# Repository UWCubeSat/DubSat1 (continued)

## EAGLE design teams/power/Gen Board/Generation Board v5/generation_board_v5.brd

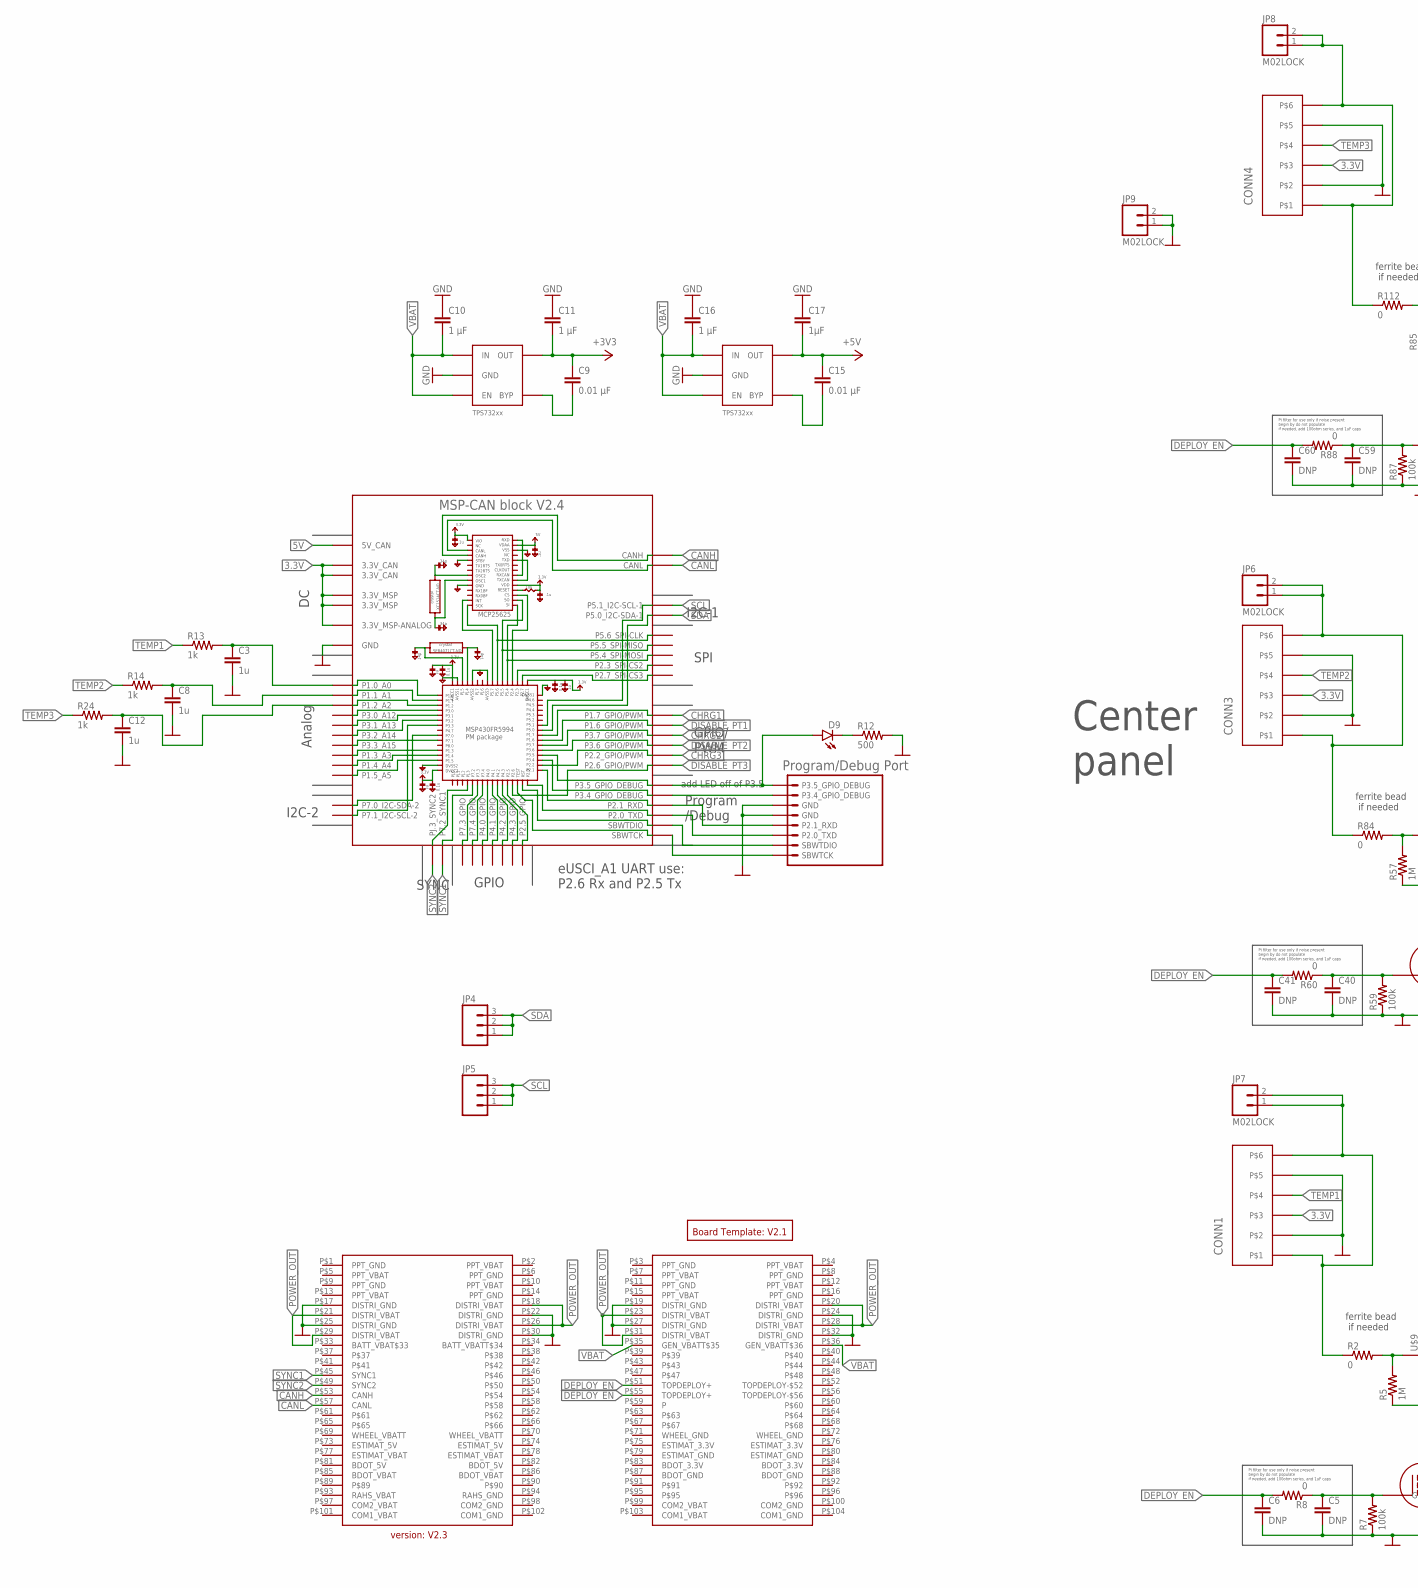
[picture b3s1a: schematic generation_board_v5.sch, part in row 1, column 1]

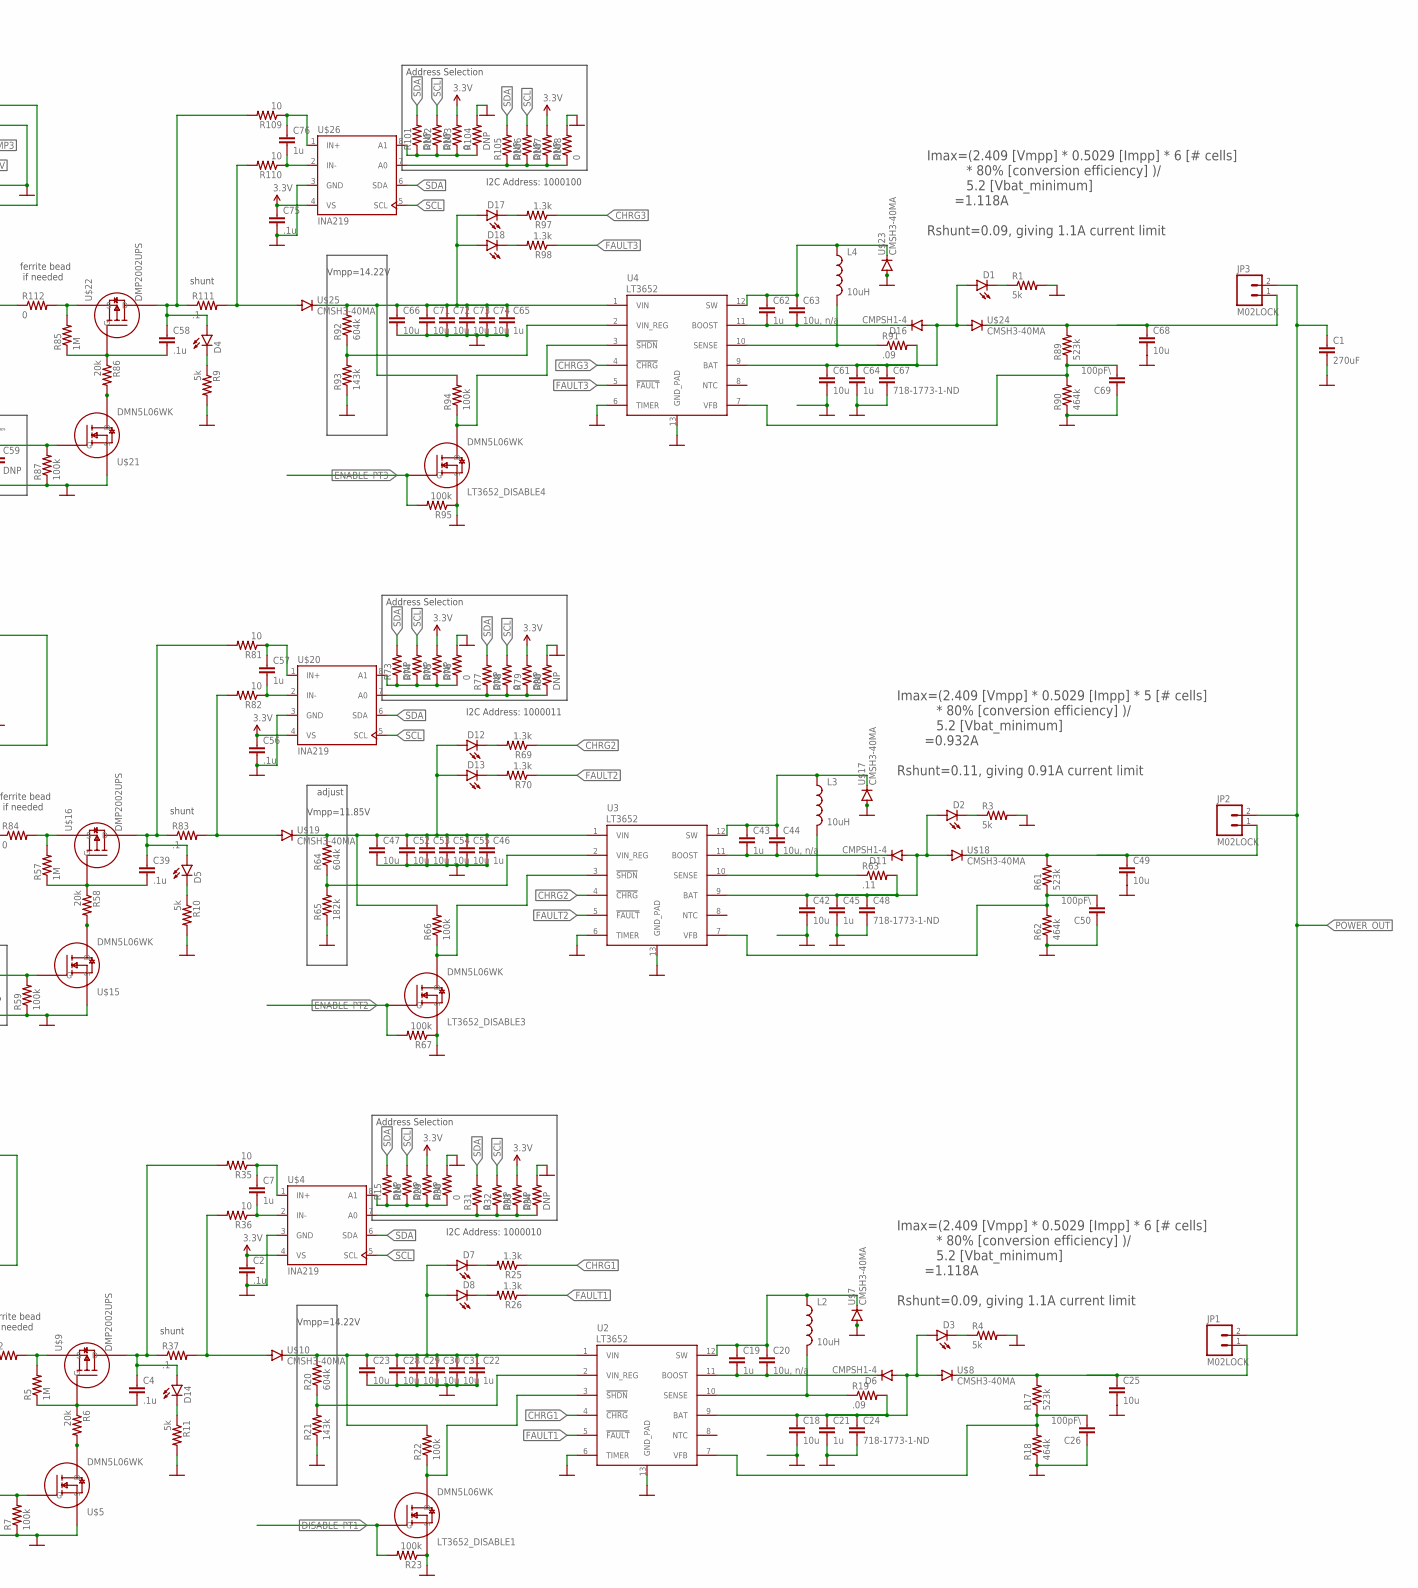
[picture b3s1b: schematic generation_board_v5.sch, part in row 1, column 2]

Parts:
BLK1: MSP-CAN_BLOCK
C1: 270uF; PANASONIC_SVPG
C2, C4, C39, C56, C58, C75: .1u; 0805
C3, C7, C8, C12, C19, C21, C22, C43, C45, C46, C57, C62, C64, C65, C76: 1u; 0805
C5, C6, C40, C41, C59, C60: DNP; 0805
C9, C15: 0.01 μF; 0805
C10, C11, C16: 1 μF; 0805
C17: 1μF; 0805
C18, C25, C42, C49, C61, C68: 10u; 0805
C20, C44, C63: 10u, n/a; 0805
C23, C28, C29, C30, C31, C47, C52, C53, C54, C55, C66, C71, C72, C73, C74: 10u; 1210
C24, C48, C67: 718-1773-1-ND; 2917
C26, C50, C69: 100pF\; 0805
CONN1, CONN3, CONN4: PICOLOCK_6
D1, D2, D3, D4, D5, D7, D8, D9, D12, D13, D14, D17, D18: LED; LED-1206
D6, D11, D16: CMPSH1-4; SOT23-3
JP1, JP2, JP3, JP6, JP7, JP8, JP9: M02LOCK; 1X02_LOCK
JP4, JP5: M03LOCK; 1X03_LOCK
L2, L3, L4: 10uH; VISHAY_SERIES_01
LT3652_DISABLE1, LT3652_DISABLE3, LT3652_DISABLE4: DMN5L06WK; SOT-323
R1, R3, R4, R9, R10, R11: 5k; 0805
R2, R8, R30, R31, R60, R76, R78, R84, R88, R103, R108, R112: 0; 0805
R5, R57, R85: 1M; 0805
R6, R58, R86: 20k; 0805
R7, R22, R23, R59, R66, R67, R87, R94, R95: 100k; 0805
R12: 500; 0805
R13, R14, R24: 1k; 0805
R15, R16, R29, R32, R33, R34, R73, R74, R75, R77, R79, R80, R101, R102, R104, R105, R106, R107: DNP; 0805
R17, R61, R89: 523k; 0805
R18, R62, R90: 464k; 0805
R19, R91: .09; R2010
R20, R64, R92: 604k; 0805
R21, R93: 143k; 0805
R25, R26, R69, R70, R97, R98: 1.3k; 0805
R35, R36, R81, R82, R109, R110: 10; 0805
R37, R83, R111: .1; R2010
R63: .11; R2010
R65: 182k; 0805
U2, U3, U4: LT3652; MSOP-12_GND
U5, U7: TPS732XX; SOT-23-5
U$1: PC104_CONNECTOR
U$2: BOARD_TEMPLATE1; BOARD_TEMPLATE
U$3: PROGRAM/DEBUG_PORT; 1X08_CONNECTOR
U$4, U$20, U$26: INA219; SOT-23-8
U$5, U$15, U$21: DMN5L06WK; SOT-323
U$7, U$8, U$10, U$17, U$18, U$19, U$23, U$24, U$25: CMSH3-40MA; SMA-DIODE
U$9, U$16, U$22: DMP2002UPS; POWERDI5060-8

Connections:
3.3V: BLK1.3.3V@CAN1 (3.3V_CAN), BLK1.3.3V@CAN2 (3.3V_CAN), BLK1.3.3V@MSP1 (3.3V_MSP), BLK1.3.3V@MSP2 (3.3V_MSP), BLK1.3.3V_ANALOG@MSP2 (3.3V_MSP-ANALOG), C2.1, C9.1, C11.2, C56.1, C75.1, CONN1.P$3, CONN3.P$3, CONN4.P$3, R29.2, R33.2, R75.2, R79.2, R103.2, R107.2, U5.P$5 (OUT), U$4.4 (VS), U$20.4 (VS), U$26.4 (VS)
5V: BLK1.5V (5V_CAN), C15.1, C17.2, U7.P$5 (OUT)
BAT1: C18.1, C21.1, C24.1, D3.A, D6.1 (A), R19.2, U2.9 (BAT), U$8.A
BAT2: C42.1, C45.1, C48.1, D2.A, D11.1 (A), R63.2, U3.9 (BAT), U$18.A
BAT3: C61.1, C64.1, C67.1, D1.A, D16.1 (A), R91.2, U4.9 (BAT), U$24.A
BOOST1: C19.2, C20.2, D6.3 (C), U2.11 (BOOST)
BOOST2: C43.2, C44.2, D11.3 (C), U3.11 (BOOST)
BOOST3: C62.2, C63.2, D16.3 (C), U4.11 (BOOST)
CANH: BLK1.CANH, U$1.P$53 (CANH)
CANL: BLK1.CANL, U$1.P$57 (CANL)
CHRG1: BLK1.P1.7_GPIO/PWM, R25.1, U2.4 (!CHRG)
CHRG2: BLK1.P3.7_GPIO/PWM, R69.1, U3.4 (!CHRG)
CHRG3: BLK1.P2.2_GPIO/PWM, R97.1, U4.4 (!CHRG)
DEPLOY_EN: C6.1, C41.1, C60.1, R8.2, R60.2, R88.2, U$1.P$51 (TOPDEPLOY+), U$1.P$55 (TOPDEPLOY+)
DISABLE_PT1: BLK1.P1.6_GPIO/PWM, LT3652_DISABLE1.1 (G), R23.2
DISABLE_PT2: BLK1.P3.6_GPIO/PWM
DISABLE_PT3: BLK1.P2.6_GPIO/PWM
ENABLE_PT2: LT3652_DISABLE3.1 (G), R67.2
ENABLE_PT3: LT3652_DISABLE4.1 (G), R95.2
FAULT1: R26.1, U2.5 (!FAULT)
FAULT2: R70.1, U3.5 (!FAULT)
FAULT3: R98.1, U4.5 (!FAULT)
GND: BLK1.GND@1 (GND), BLK1.GND@2 (GND), BLK1.GND@3 (GND), BLK1.GND@4 (GND), BLK1.GND@5 (GND), BLK1.GND@7 (GND), BLK1.GND@8 (GND), BLK1.GND@9 (GND), BLK1.GND@10 (GND), BLK1.GND@11 (GND), BLK1.GND@12 (GND), BLK1.GND@13 (GND), BLK1.GND@14 (GND), BLK1.GND@15 (GND), BLK1.GND@16 (GND), BLK1.GND@17 (GND), BLK1.GND@26 (GND), C1.NEG (2), C2.2, C3.2, C5.2, C6.2, C8.2, C10.1, C11.1, C12.2, C16.1, C17.1, C18.2, C21.2, C22.2, C23.2, C24.2, C25.2, C26.1, C28.2, C29.2, C30.2, C31.2, C40.2, C41.2, C42.2, C45.2, C46.2, C47.2, C48.2, C49.2, C50.1, C52.2, C53.2, C54.2, C55.2, C56.2, C59.2, C60.2, C61.2, C64.2, C65.2, C66.2, C67.2, C68.2, C69.1, C71.2, C72.2, C73.2, C74.2, C75.2, CONN1.P$2, CONN1.P$5, CONN3.P$2, CONN3.P$5, CONN4.P$2, CONN4.P$5, JP9.1, JP9.2, LT3652_DISABLE1.2 (S), LT3652_DISABLE3.2 (S), LT3652_DISABLE4.2 (S), R1.2, R3.2, R4.2, R7.1, R9.2, R10.2, R11.2, R12.2, R18.1, R21.1, R23.1, R30.2, R34.2, R59.1, R62.1, R65.1, R67.1, R76.2, R80.2, R87.1, R90.1, R93.1, R95.1, R104.2, R108.2, U2.6 (TIMER), U2.13 (GND_PAD), U3.6 (TIMER), U3.13 (GND_PAD), U4.6 (TIMER), U4.13 (GND_PAD), U5.P$2 (GND), U7.P$2 (GND), U$1.P$17 (DISTRI_GND), U$1.P$19 (DISTRI_GND), U$1.P$22 (DISTRI_GND), U$1.P$24 (DISTRI_GND), U$1.P$25 (DISTRI_GND), U$1.P$27 (DISTRI_GND), U$1.P$30 (DISTRI_GND), U$1.P$32 (DISTRI_GND), U$3.5 (GND), U$3.6 (GND), U$4.3 (GND), U$5.2 (S), U$7.A, U$15.2 (S), U$17.A, U$20.3 (GND), U$21.2 (S), U$23.A, U$26.3 (GND)
IN1: R2.2, R5.2, U$9.S1 (S), U$9.S2 (S), U$9.S3 (S)
IN2: R57.2, R84.2, U$16.S1 (S), U$16.S2 (S), U$16.S3 (S)
IN3: R85.2, R112.2, U$22.S1 (S), U$22.S2 (S), U$22.S3 (S)
INA219_A0_1: R31.1, R32.1, R33.1, R34.1, U$4.7 (A0)
INA219_A0_2: R77.1, R78.1, R79.1, R80.1, U$20.7 (A0)
INA219_A0_3: R105.1, R106.1, R107.1, R108.1, U$26.7 (A0)
INA219_A1_1: R15.1, R16.1, R29.1, R30.1, U$4.8 (A1)
INA219_A1_2: R73.1, R74.1, R75.1, R76.1, U$20.8 (A1)
INA219_A1_3: R101.1, R102.1, R103.1, R104.1, U$26.8 (A1)
INA219_IN+_1: C7.1, R35.1, U$4.1 (IN+)
INA219_IN+_2: C57.1, R81.1, U$20.1 (IN+)
INA219_IN+_3: C76.1, R109.1, U$26.1 (IN+)
INA219_IN-_1: C7.2, R36.1, U$4.2 (IN-)
INA219_IN-_2: C57.2, R82.1, U$20.2 (IN-)
INA219_IN-_3: C76.2, R110.1, U$26.2 (IN-)
INPUT_PANEL1: CONN1.P$1, CONN1.P$6, JP7.1, JP7.2, R2.1
INPUT_PANEL2: CONN3.P$1, CONN3.P$6, JP6.1, JP6.2, R84.1
INPUT_PANEL3: CONN4.P$1, CONN4.P$6, JP8.1, JP8.2, R112.1
LDO_3V3_BYP2: C9.2, U5.P$4 (BYP)
LDO_5V_BYP2: C15.2, U7.P$4 (BYP)
LOAD1: R36.2, R37.2, U$10.A
LOAD2: R82.2, R83.2, U$19.A
LOAD3: R110.2, R111.2, U$25.A
unnamed: C4.2, R5.1, R6.1, U$9.G
unnamed: C5.1, R7.2, R8.1, U$5.1 (G)
unnamed: BLK1.P3.5_GPIO_DEBUG, D9.A, U$3.8 (P3.5_GPIO_DEBUG)
unnamed: BLK1.P3.4_GPIO_DEBUG, U$3.7 (P3.4_GPIO_DEBUG)
unnamed: BLK1.P2.1_RXD, U$3.4 (P2.1_RXD)
unnamed: R6.2, U$5.3 (D)
unnamed: BLK1.P2.0_TXD, U$3.3 (P2.0_TXD)
unnamed: BLK1.SBWTDIO, U$3.2 (SBWTDIO)
unnamed: BLK1.SBWTCK, U$3.SBWTCK
unnamed: D1.C, R1.1
unnamed: D2.C, R3.1
unnamed: D3.C, R4.1
unnamed: D4.C, R9.1
unnamed: C39.2, R57.1, R58.1, U$16.G
unnamed: C40.1, R59.2, R60.1, U$15.1 (G)
unnamed: LT3652_DISABLE1.3 (D), R22.1, U2.3 (!SHDN)
unnamed: D8.C, R26.2
unnamed: D7.C, R25.2
unnamed: R58.2, U$15.3 (D)
unnamed: BLK1.P1.1_A1, C8.1, R14.2
unnamed: D9.C, R12.1
unnamed: LT3652_DISABLE3.3 (D), R66.1, U3.3 (!SHDN)
unnamed: D13.C, R70.2
unnamed: D12.C, R69.2
unnamed: D14.C, R11.1
unnamed: D5.C, R10.1
unnamed: C58.2, R85.1, R86.1, U$22.G
unnamed: C59.1, R87.2, R88.1, U$21.1 (G)
unnamed: R86.2, U$21.3 (D)
unnamed: LT3652_DISABLE4.3 (D), R94.1, U4.3 (!SHDN)
unnamed: D18.C, R98.2
unnamed: D17.C, R97.2
unnamed: BLK1.P1.2_A2, C12.1, R24.2
unnamed: BLK1.P1.0_A0, C3.1, R13.2
OUT1: C4.1, D14.A, R35.2, R37.1, U$9.D1 (D), U$9.D2 (D), U$9.D3 (D), U$9.D4 (D), U$9.D5 (D)
OUT2: C39.1, D5.A, R81.2, R83.1, U$16.D1 (D), U$16.D2 (D), U$16.D3 (D), U$16.D4 (D), U$16.D5 (D)
OUT3: C58.1, D4.A, R109.2, R111.1, U$22.D1 (D), U$22.D2 (D), U$22.D3 (D), U$22.D4 (D), U$22.D5 (D)
OUTPUT1: C25.1, JP1.1, R17.2, U$8.C
OUTPUT2: C49.1, JP2.1, R61.2, U$18.C
OUTPUT3: C68.1, JP3.1, R89.2, U$24.C
POWER_OUT: C1.POS (1), JP1.2, JP2.2, JP3.2, U$1.P$18 (DISTRI_VBAT), U$1.P$20 (DISTRI_VBAT), U$1.P$21 (DISTRI_VBAT), U$1.P$23 (DISTRI_VBAT), U$1.P$26 (DISTRI_VBAT), U$1.P$28 (DISTRI_VBAT), U$1.P$29 (DISTRI_VBAT), U$1.P$31 (DISTRI_VBAT)
SCL: BLK1.P5.1_I2C-SCL-1, JP5.1, JP5.2, JP5.3, R16.2, R32.2, R74.2, R78.2, R102.2, R106.2, U$4.5 (SCL), U$20.5 (SCL), U$26.5 (SCL)
SDA: BLK1.P5.0_I2C-SDA-1, JP4.1, JP4.2, JP4.3, R15.2, R31.2, R73.2, R77.2, R101.2, R105.2, U$4.6 (SDA), U$20.6 (SDA), U$26.6 (SDA)
SENSE1: L2.P$2 (2), R19.1, U2.10 (SENSE)
SENSE2: L3.P$2 (2), R63.1, U3.10 (SENSE)
SENSE3: L4.P$2 (2), R91.1, U4.10 (SENSE)
SW1: C19.1, C20.1, L2.P$1 (1), U2.12 (SW), U$7.C
SW2: C43.1, C44.1, L3.P$1 (1), U3.12 (SW), U$17.C
SW3: C62.1, C63.1, L4.P$1 (1), U4.12 (SW), U$23.C
SYNC1: BLK1.P7.2_SYNC1, U$1.P$45 (SYNC1)
SYNC2: BLK1.PJ.3_SYNC2, U$1.P$49 (SYNC2)
TEMP1: CONN1.P$4, R13.1
TEMP2: CONN3.P$4, R14.1
TEMP3: CONN4.P$4, R24.1
VBAT: C10.2, C16.2, U5.P$1 (IN), U5.P$3 (EN), U7.P$1 (IN), U7.P$3 (EN), U$1.P$35 (GEN_VBATT$35), U$1.P$36 (GEN_VBATT$36)
VFB1: C26.2, R17.1, R18.2, U2.7 (VFB)
VFB2: C50.2, R61.1, R62.2, U3.7 (VFB)
VFB3: C69.2, R89.1, R90.2, U4.7 (VFB)
VIN1: C22.1, C23.1, C28.1, C29.1, C30.1, C31.1, D7.A, D8.A, R20.2, R22.2, U2.1 (VIN), U$10.C
VIN2: C46.1, C47.1, C52.1, C53.1, C54.1, C55.1, D12.A, D13.A, R64.2, R66.2, U3.1 (VIN), U$19.C
VIN3: C65.1, C66.1, C71.1, C72.1, C73.1, C74.1, D17.A, D18.A, R92.2, R94.2, U4.1 (VIN), U$25.C
VIN_REG1: R20.1, R21.2, U2.2 (VIN_REG)
VIN_REG2: R64.1, R65.2, U3.2 (VIN_REG)
VIN_REG3: R92.1, R93.2, U4.2 (VIN_REG)

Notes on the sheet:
Pi filter for use only if noise present begin by do not populate if needed, add 100ohm series, and 1uF caps
Address Selection
ferrite bead if needed
shunt
adjust
Vmpp=14.22V
Center panel
Imax=(2.409 [Vmpp] * 0.5029 [Impp] * 6 [# cells] * 80% [conversion efficiency] )/ 5.2 [Vbat_minimum] =1.118A Rshunt=0.09, giving 1.1A current limit
Imax=(2.409 [Vmpp] * 0.5029 [Impp] * 5 [# cells] * 80% [conversion efficiency] )/ 5.2 [Vbat_minimum] =0.932A Rshunt=0.11, giving 0.91A current limit
Vmpp=11.85V
I2C Address: 1000010
I2C Address: 1000011
I2C Address: 1000100

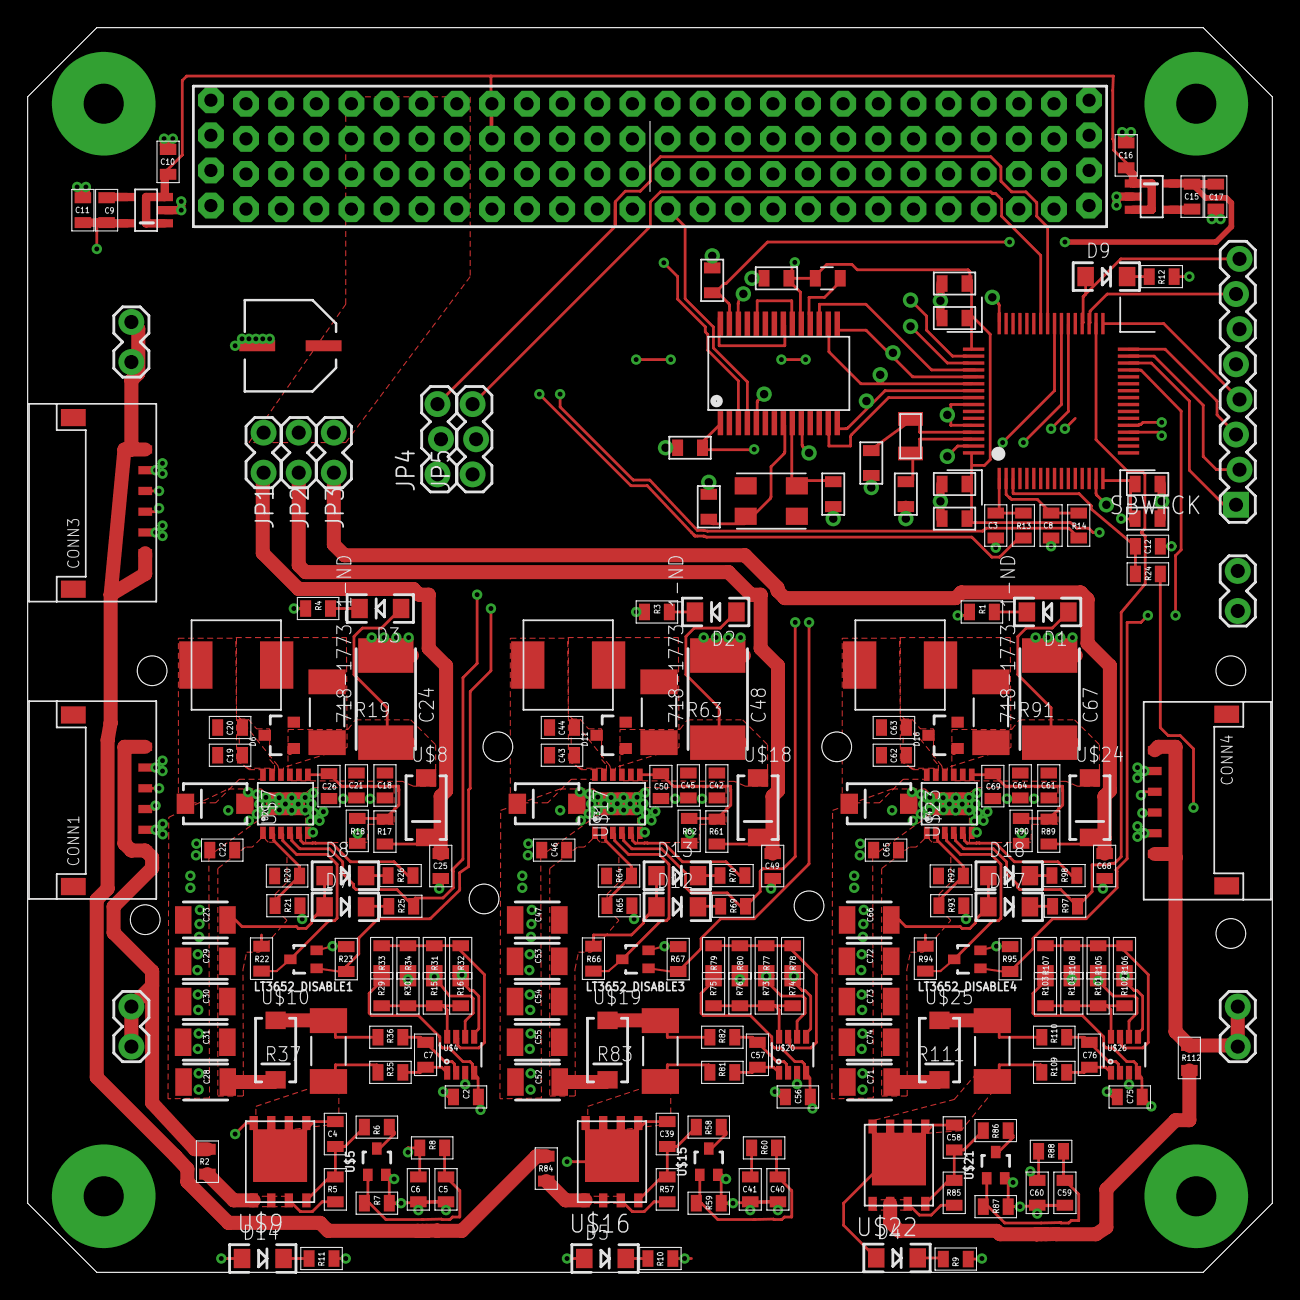
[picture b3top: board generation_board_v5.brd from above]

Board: 4 copper layers, 90.0 x 90.0 mm, 218 parts (0 on the bottom side), 108 nets.

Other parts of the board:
U$6, U$11, U$12, U$13, U$14, U$27, U$28, U$29: #2-56_BOLT_HOLE

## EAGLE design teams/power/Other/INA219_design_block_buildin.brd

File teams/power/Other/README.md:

This folder is for usefull resources such as eagle libraries, cam processors and such. Not for documentation

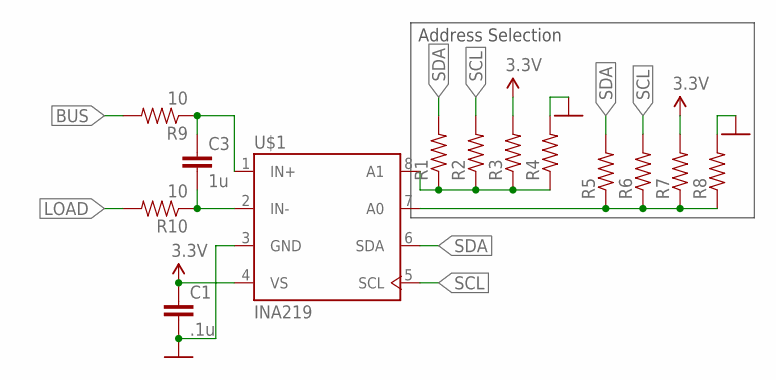
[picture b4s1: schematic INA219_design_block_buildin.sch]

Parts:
C1: .1u; 0805
C3: 1u; 0805
R1, R2, R3, R4, R5, R6, R7, R8: RESISTOR0805; 0805
R9, R10: 10; 0805
U$1: INA219; SOT-23-8

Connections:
3.3V: C1.1, R3.2, R7.2, U$1.4 (VS)
BUS: R9.2
GND: C1.2, R4.2, R8.2, U$1.3 (GND)
INA219_A0: R5.1, R6.1, R7.1, R8.1, U$1.7 (A0)
INA219_A1: R1.1, R2.1, R3.1, R4.1, U$1.8 (A1)
INA219_IN+: C3.1, R9.1, U$1.1 (IN+)
INA219_IN-: C3.2, R10.1, U$1.2 (IN-)
LOAD: R10.2
SCL: R2.2, R6.2, U$1.5 (SCL)
SDA: R1.2, R5.2, U$1.6 (SDA)

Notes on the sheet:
Address Selection

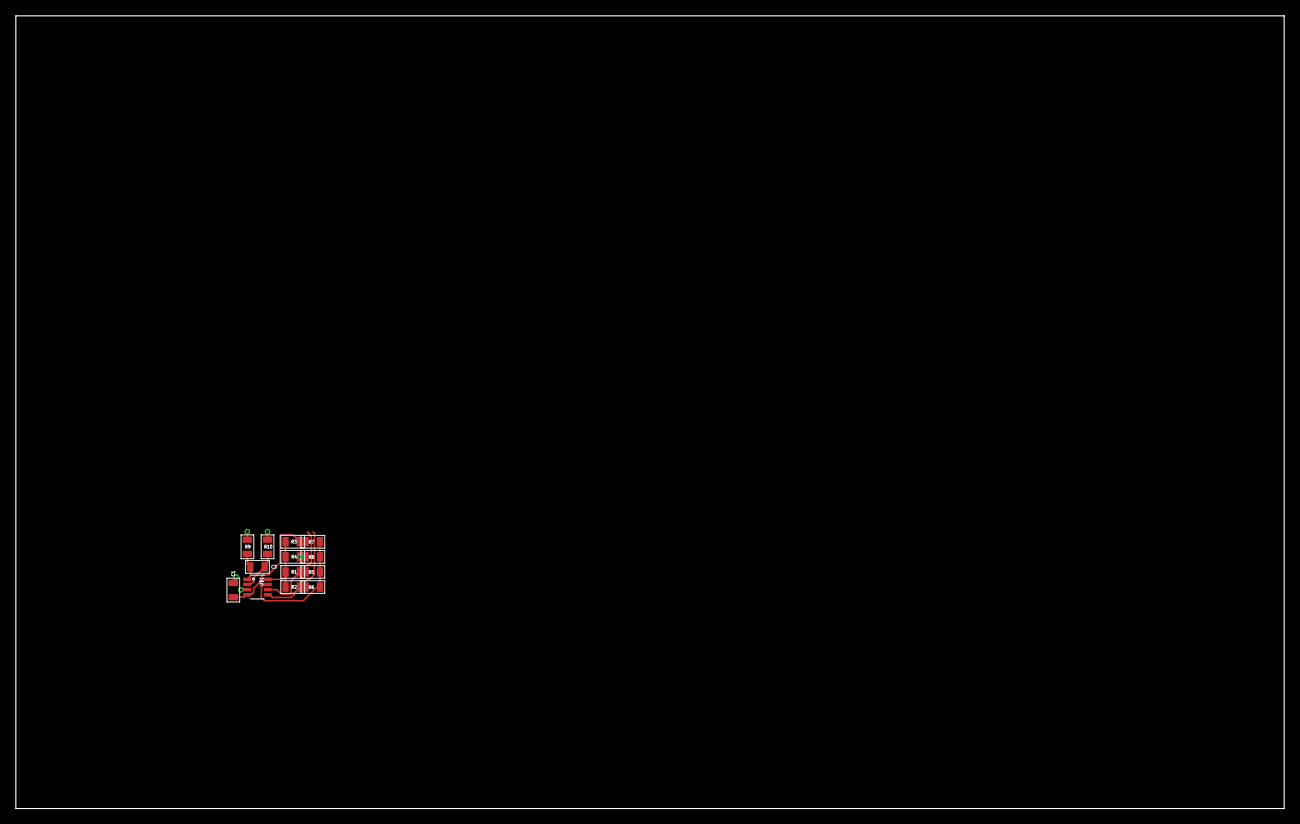
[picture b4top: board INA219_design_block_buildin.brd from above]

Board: 2 copper layers, 160.0 x 100.0 mm, 13 parts (0 on the bottom side), 8 nets.

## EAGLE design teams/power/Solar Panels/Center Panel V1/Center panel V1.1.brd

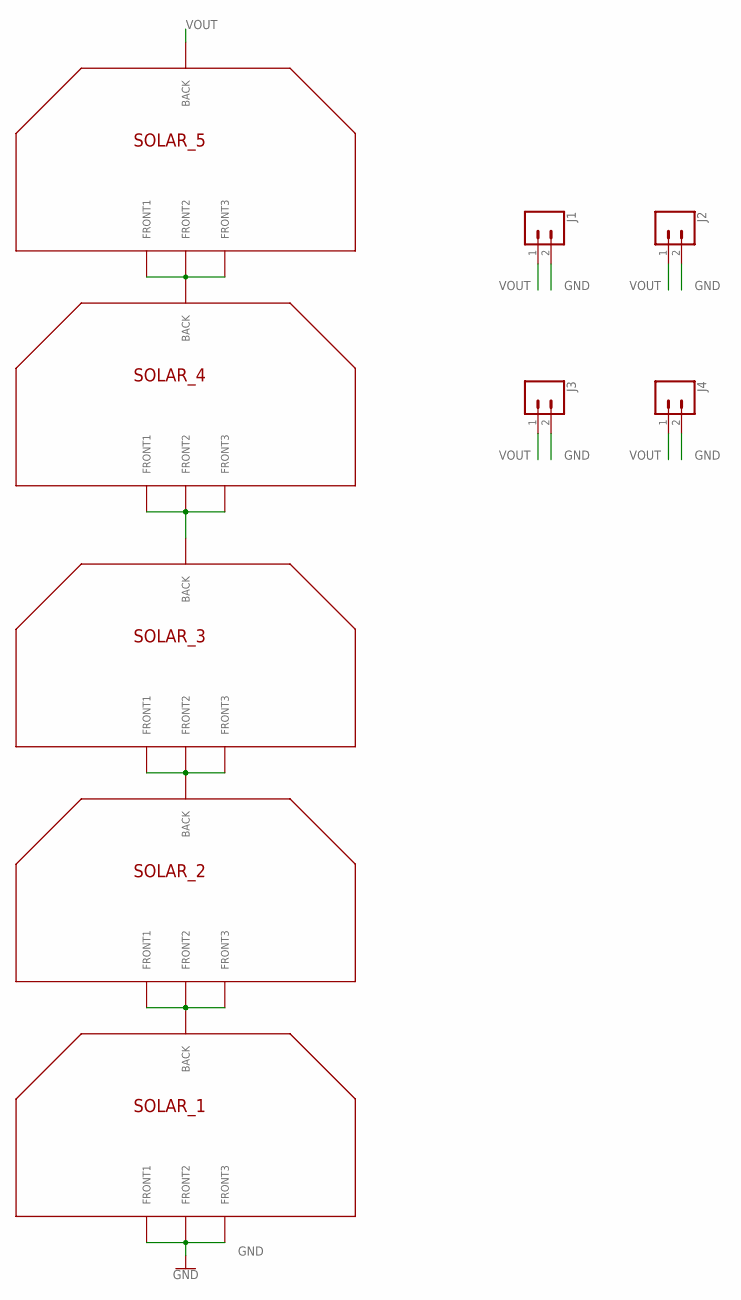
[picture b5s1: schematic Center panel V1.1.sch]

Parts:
J1, J2, J3, J4: CONN_02; 1X02
SOLAR_1, SOLAR_2, SOLAR_3, SOLAR_4, SOLAR_5: SOLAR_CELL_HALF_TABS; SOLAR_CELL_3G30A_HALF_TAB

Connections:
1-2: SOLAR_1.P$1 (BACK), SOLAR_2.P$F1 (FRONT1), SOLAR_2.P$F2 (FRONT2), SOLAR_2.P$F3 (FRONT3)
2-3: SOLAR_2.P$1 (BACK), SOLAR_3.P$F1 (FRONT1), SOLAR_3.P$F2 (FRONT2), SOLAR_3.P$F3 (FRONT3)
3-4: SOLAR_3.P$1 (BACK), SOLAR_4.P$F1 (FRONT1), SOLAR_4.P$F2 (FRONT2), SOLAR_4.P$F3 (FRONT3)
4-5: SOLAR_4.P$1 (BACK), SOLAR_5.P$F1 (FRONT1), SOLAR_5.P$F2 (FRONT2), SOLAR_5.P$F3 (FRONT3)
GND: J1.2, J2.2, J3.2, J4.2, SOLAR_1.P$F1 (FRONT1), SOLAR_1.P$F2 (FRONT2), SOLAR_1.P$F3 (FRONT3)
VOUT: J1.1, J2.1, J3.1, J4.1, SOLAR_5.P$1 (BACK)

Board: 2 copper layers, 9 parts (0 on the bottom side), 6 nets, no tracks yet.

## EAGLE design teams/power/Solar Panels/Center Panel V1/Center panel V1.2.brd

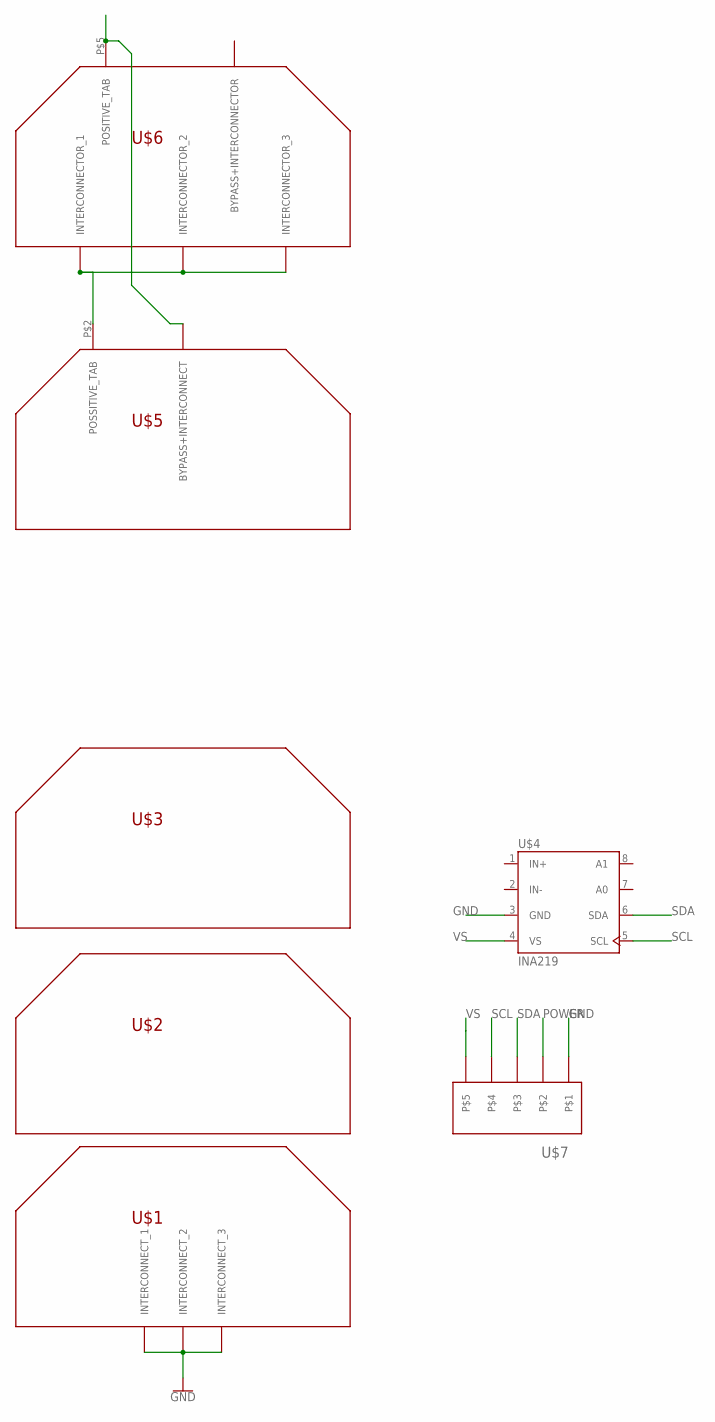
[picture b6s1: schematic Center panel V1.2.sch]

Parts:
U$1: SOLAR_CELL_BOTTOM; SOLAR_CELL_BOTTOM_SHORT-PADS
U$2, U$3: SOALAR_CELL_OUTLINE; SOLAR_CELL_OUTLINE
U$4: INA219; S008
U$5: SOLAR_CELL_TOP; SOLAR_CELL_TOP_SHORT-PAD
U$6: SOLAR_CELL_STAND-ALONE
U$7: PICOLOCK_5

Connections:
GND: U$1.P$1 (INTERCONNECT_1), U$1.P$2 (INTERCONNECT_2), U$1.P$3 (INTERCONNECT_3), U$4.3 (GND), U$7.P$1
unnamed: U$5.P$2 (POSSITIVE_TAB), U$6.P$1 (INTERCONNECTOR_1), U$6.P$2 (INTERCONNECTOR_2), U$6.P$3 (INTERCONNECTOR_3)
unnamed: U$5.P$1 (BYPASS+INTERCONNECT), U$6.P$5 (POSITIVE_TAB)
POWER: U$7.P$2
SCL: U$4.5 (SCL), U$7.P$4
SDA: U$4.6 (SDA), U$7.P$3
VS: U$4.4 (VS), U$7.P$5

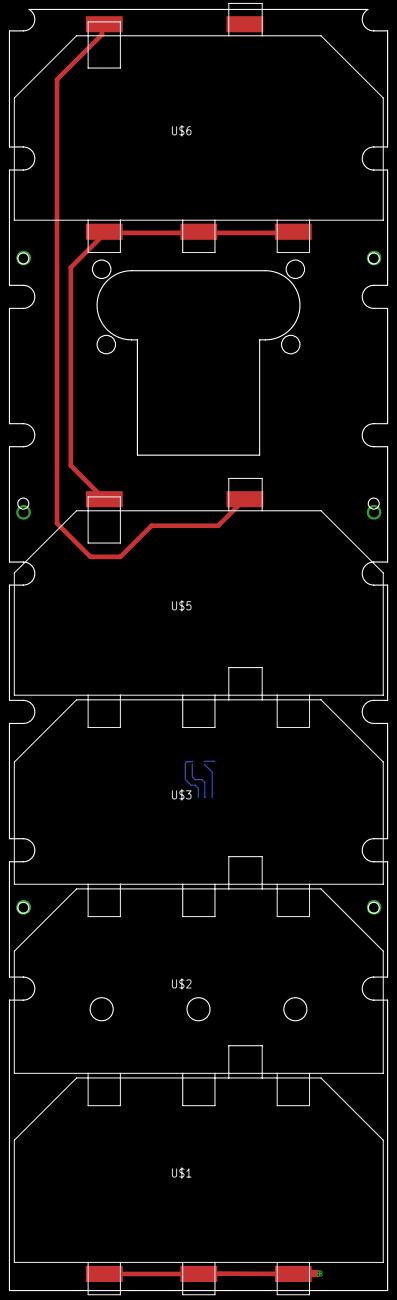
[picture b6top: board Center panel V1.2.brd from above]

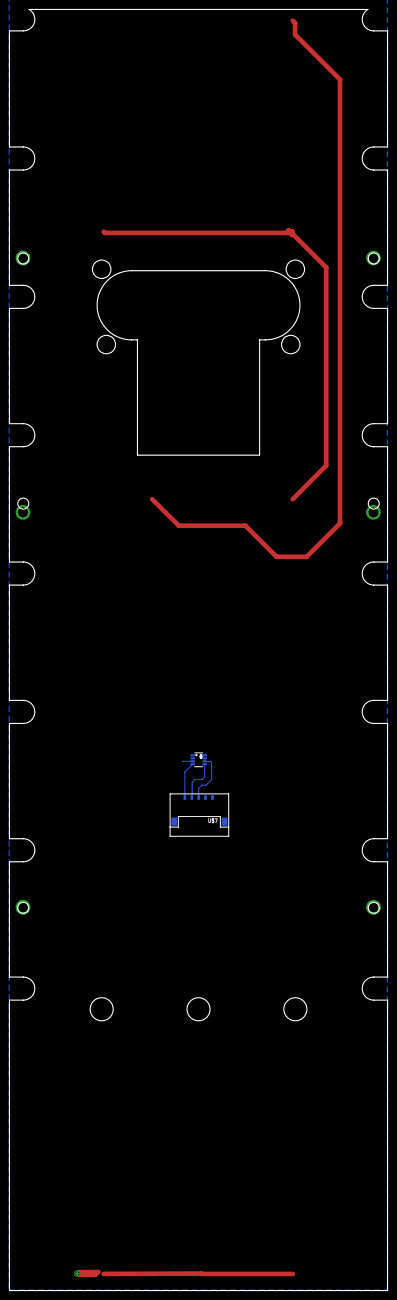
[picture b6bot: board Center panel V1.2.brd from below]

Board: 2 copper layers, 82.0 x 277.8 mm, 7 parts (2 on the bottom side), 6 nets.
